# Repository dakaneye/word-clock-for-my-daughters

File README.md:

# word-clock-for-my-daughters

Two word clocks, one for each daughter, to be delivered around their 7th birthdays.

- **Emory** — Oct 6, 2030
- **Nora** — Mar 19, 2032

Shared ESP32 + WS2812B platform, per-kid configuration (name, birthday, wood species, lullaby, hidden birthdate acrostic).

See [`docs/superpowers/specs/2026-04-14-daughters-clocks-design.md`](docs/superpowers/specs/2026-04-14-daughters-clocks-design.md) for the full design.

## Lineage

Follows the original word clock for my wife Chelsea, built 2015 and revived 2026, at [`dakaneye/word-clock`](https://github.com/dakaneye/word-clock). Same family, newer generation.

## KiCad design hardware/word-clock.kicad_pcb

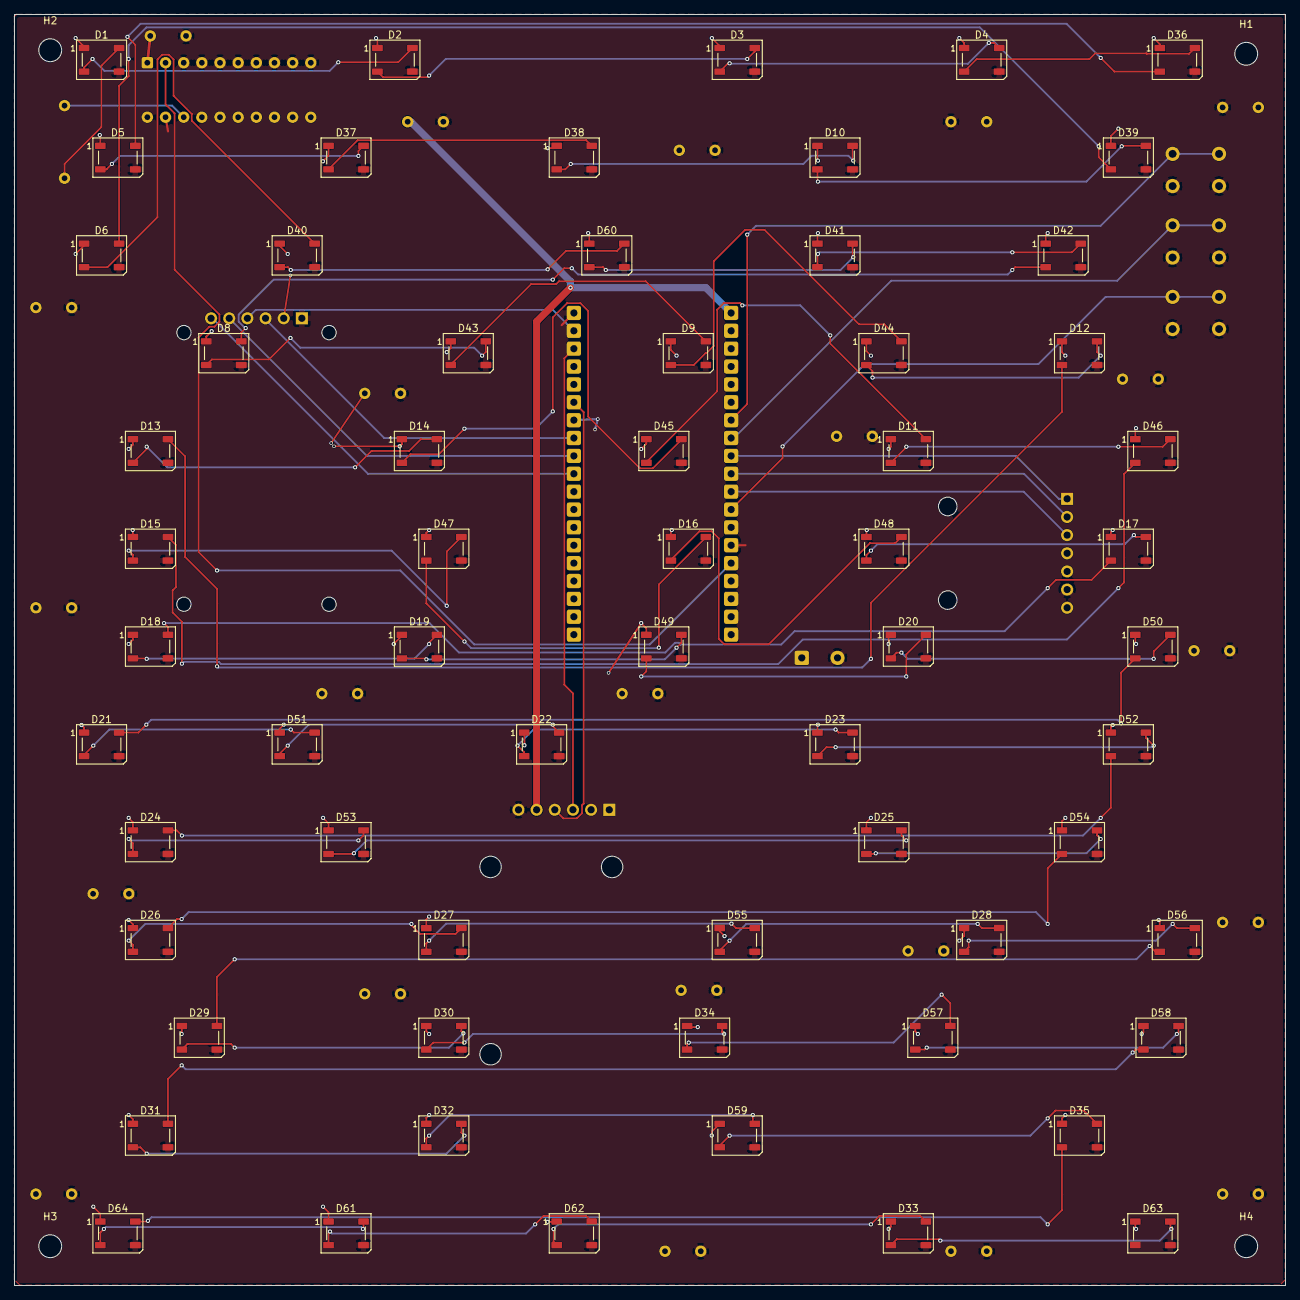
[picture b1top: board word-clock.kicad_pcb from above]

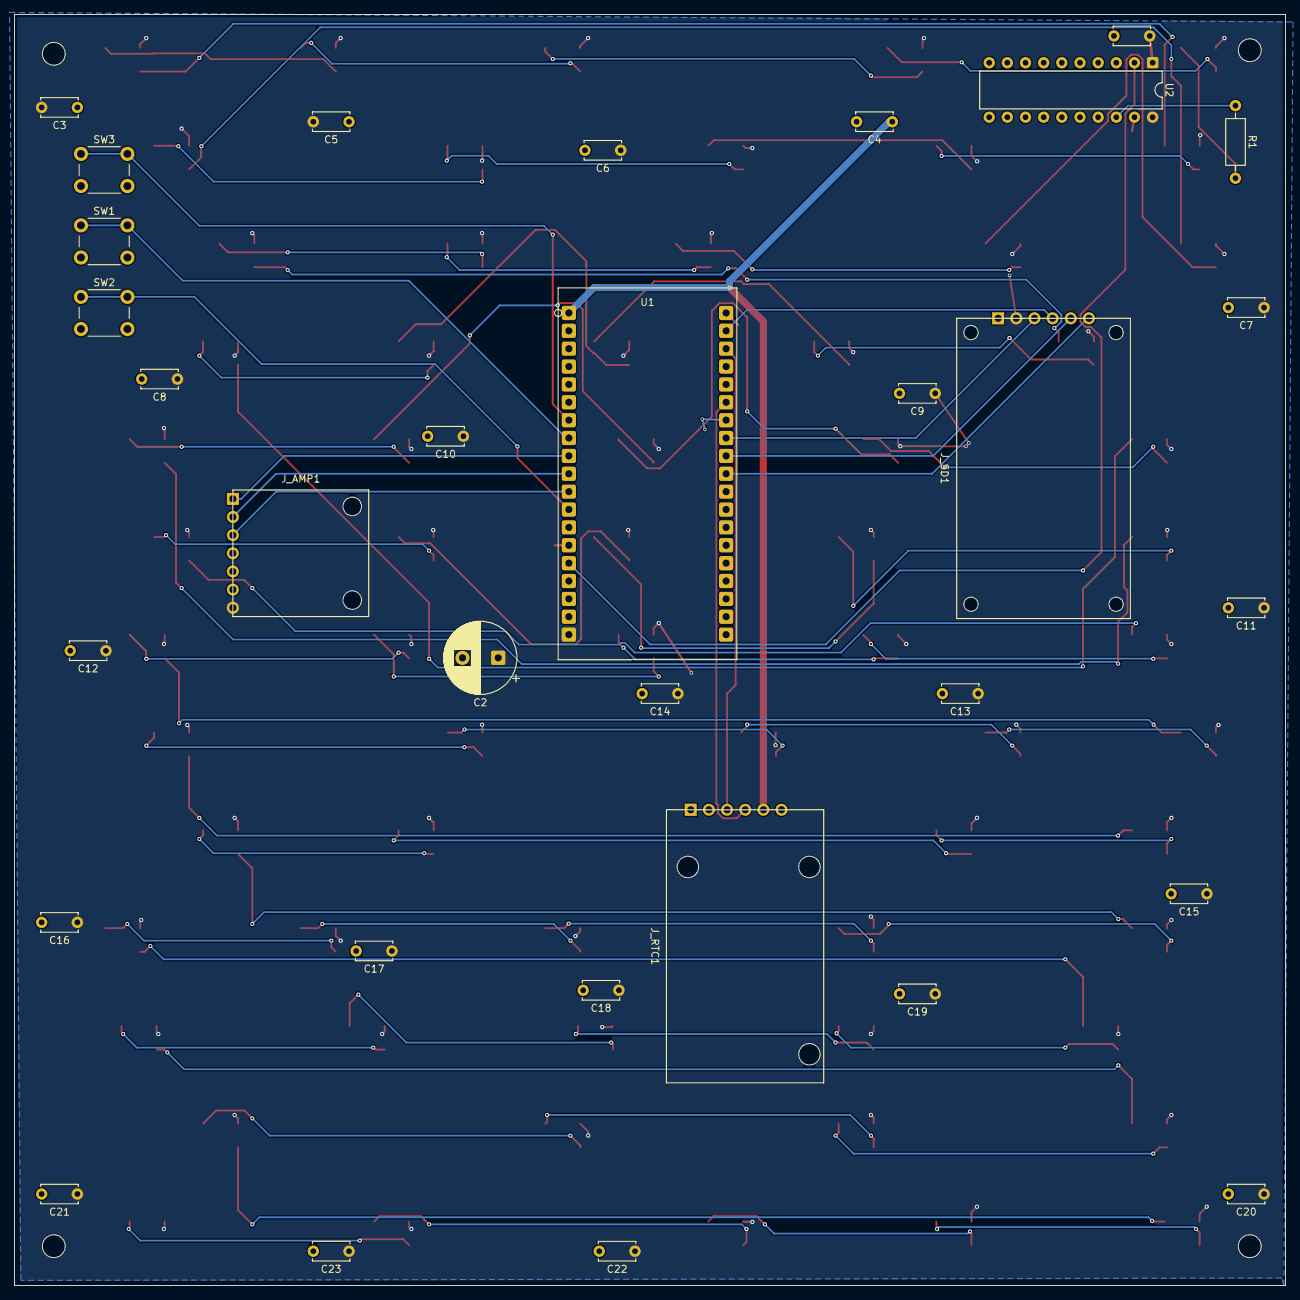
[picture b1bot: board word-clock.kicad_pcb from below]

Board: 2 copper layers, 177.8 x 177.8 mm, 99 parts (32 on the bottom side), 80 nets.

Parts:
C1, C3, C4, C5, C6, C7, C8, C9, C10, C11, C12, C13, C14, C15, C16, C17, C18, C19, C20, C21, C22, C23: 100nF; C_Disc_D5.0mm_W2.5mm_P5.00mm
C2: 1000µF / 10V; CP_Radial_D10.0mm_P5.00mm
D1: LED_IT; LED_WS2812B_PLCC4_5.0x5.0mm_P3.2mm
D2: LED_IS; LED_WS2812B_PLCC4_5.0x5.0mm_P3.2mm
D3: LED_TEN_MIN; LED_WS2812B_PLCC4_5.0x5.0mm_P3.2mm
D4: LED_HALF; LED_WS2812B_PLCC4_5.0x5.0mm_P3.2mm
D5: LED_QUARTER; LED_WS2812B_PLCC4_5.0x5.0mm_P3.2mm
D6: LED_FIVE_MIN; LED_WS2812B_PLCC4_5.0x5.0mm_P3.2mm
D8: LED_HAPPY; LED_WS2812B_PLCC4_5.0x5.0mm_P3.2mm
D9: LED_PAST; LED_WS2812B_PLCC4_5.0x5.0mm_P3.2mm
D10: LED_TWENTY; LED_WS2812B_PLCC4_5.0x5.0mm_P3.2mm
D11: LED_THREE; LED_WS2812B_PLCC4_5.0x5.0mm_P3.2mm
D12: LED_TO; LED_WS2812B_PLCC4_5.0x5.0mm_P3.2mm
D13: LED_ONE; LED_WS2812B_PLCC4_5.0x5.0mm_P3.2mm
D14: LED_BIRTH; LED_WS2812B_PLCC4_5.0x5.0mm_P3.2mm
D15: LED_ELEVEN; LED_WS2812B_PLCC4_5.0x5.0mm_P3.2mm
D16: LED_FOUR; LED_WS2812B_PLCC4_5.0x5.0mm_P3.2mm
D17: LED_DAY; LED_WS2812B_PLCC4_5.0x5.0mm_P3.2mm
D18: LED_TWO; LED_WS2812B_PLCC4_5.0x5.0mm_P3.2mm
D19: LED_EIGHT; LED_WS2812B_PLCC4_5.0x5.0mm_P3.2mm
D20: LED_SEVEN; LED_WS2812B_PLCC4_5.0x5.0mm_P3.2mm
D21: LED_NINE; LED_WS2812B_PLCC4_5.0x5.0mm_P3.2mm
D22: LED_SIX; LED_WS2812B_PLCC4_5.0x5.0mm_P3.2mm
D23: LED_TWELVE; LED_WS2812B_PLCC4_5.0x5.0mm_P3.2mm
D24: LED_NAME; LED_WS2812B_PLCC4_5.0x5.0mm_P3.2mm
D25: LED_FIVE_HR; LED_WS2812B_PLCC4_5.0x5.0mm_P3.2mm
D26: LED_TEN_HR; LED_WS2812B_PLCC4_5.0x5.0mm_P3.2mm
D27: LED_OCLOCK; LED_WS2812B_PLCC4_5.0x5.0mm_P3.2mm
D28: LED_NOON; LED_WS2812B_PLCC4_5.0x5.0mm_P3.2mm
D29: LED_IN; LED_WS2812B_PLCC4_5.0x5.0mm_P3.2mm
D30: LED_THE; LED_WS2812B_PLCC4_5.0x5.0mm_P3.2mm
D31: LED_AFTERNOON; LED_WS2812B_PLCC4_5.0x5.0mm_P3.2mm
D32: LED_AFTERNOON_1; LED_WS2812B_PLCC4_5.0x5.0mm_P3.2mm
D33: LED_NIGHT; LED_WS2812B_PLCC4_5.0x5.0mm_P3.2mm
D34: LED_MORNING; LED_WS2812B_PLCC4_5.0x5.0mm_P3.2mm
D35: LED_AT; LED_WS2812B_PLCC4_5.0x5.0mm_P3.2mm
D36: LED_HALF_1; LED_WS2812B_PLCC4_5.0x5.0mm_P3.2mm
D37: LED_QUARTER_1; LED_WS2812B_PLCC4_5.0x5.0mm_P3.2mm
D38: LED_QUARTER_2; LED_WS2812B_PLCC4_5.0x5.0mm_P3.2mm
D39: LED_TWENTY_1; LED_WS2812B_PLCC4_5.0x5.0mm_P3.2mm
D40: LED_FIVE_MIN_1; LED_WS2812B_PLCC4_5.0x5.0mm_P3.2mm
D41: LED_MINUTES_1; LED_WS2812B_PLCC4_5.0x5.0mm_P3.2mm
D42: LED_MINUTES_2; LED_WS2812B_PLCC4_5.0x5.0mm_P3.2mm
D43: LED_HAPPY_1; LED_WS2812B_PLCC4_5.0x5.0mm_P3.2mm
D44: LED_PAST_1; LED_WS2812B_PLCC4_5.0x5.0mm_P3.2mm
D45: LED_BIRTH_1; LED_WS2812B_PLCC4_5.0x5.0mm_P3.2mm
D46: LED_THREE_1; LED_WS2812B_PLCC4_5.0x5.0mm_P3.2mm
D47: LED_ELEVEN_1; LED_WS2812B_PLCC4_5.0x5.0mm_P3.2mm
D48: LED_FOUR_1; LED_WS2812B_PLCC4_5.0x5.0mm_P3.2mm
D49: LED_EIGHT_1; LED_WS2812B_PLCC4_5.0x5.0mm_P3.2mm
D50: LED_SEVEN_1; LED_WS2812B_PLCC4_5.0x5.0mm_P3.2mm
D51: LED_NINE_1; LED_WS2812B_PLCC4_5.0x5.0mm_P3.2mm
D52: LED_TWELVE_1; LED_WS2812B_PLCC4_5.0x5.0mm_P3.2mm
D53: LED_NAME_1; LED_WS2812B_PLCC4_5.0x5.0mm_P3.2mm
D54: LED_FIVE_HR_1; LED_WS2812B_PLCC4_5.0x5.0mm_P3.2mm
D55: LED_OCLOCK_1; LED_WS2812B_PLCC4_5.0x5.0mm_P3.2mm
D56: LED_NOON_1; LED_WS2812B_PLCC4_5.0x5.0mm_P3.2mm
D57: LED_MORNING_1; LED_WS2812B_PLCC4_5.0x5.0mm_P3.2mm
D58: LED_MORNING_2; LED_WS2812B_PLCC4_5.0x5.0mm_P3.2mm
D59: LED_AFTERNOON_2; LED_WS2812B_PLCC4_5.0x5.0mm_P3.2mm
D60: LED_MINUTES; LED_WS2812B_PLCC4_5.0x5.0mm_P3.2mm
D61: LED_EVENING_1; LED_WS2812B_PLCC4_5.0x5.0mm_P3.2mm
D62: LED_EVENING_2; LED_WS2812B_PLCC4_5.0x5.0mm_P3.2mm
D63: LED_NIGHT_1; LED_WS2812B_PLCC4_5.0x5.0mm_P3.2mm
D64: LED_EVENING; LED_WS2812B_PLCC4_5.0x5.0mm_P3.2mm
H1, H2, H3, H4: MountingHole_3.2mm_M3
J_AMP1: MAX98357A breakout; Daughtercard_AMP_MAX98357A
J_RTC1: DS3231 ZS-042; Daughtercard_RTC_DS3231
J_SD1: HW-125 microSD; Daughtercard_SD_HW125
R1: Resistor 300 ohm; R_Axial_DIN0207_L6.3mm_D2.5mm_P10.16mm_Horizontal
SW1: Minute; SW_PUSH_6mm
SW2: Audio; SW_PUSH_6mm
SW3: Hour; SW_PUSH_6mm
U1: ESP32 CP2102; ESP32_38Pin
U2: 74HCT245; DIP-20_W7.62mm

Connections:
+3V3: C4.1, J_RTC1.2 (VCC_5), U1.1 (3V3)
+5V: C1.1, C2.1, C3.2, C5.2, C6.1, C7.1, C8.1, C9.1, C10.1, C11.1, C12.1, C13.1, C14.1, C15.1, C16.1, C17.1, C18.1, C19.1, C20.1, C21.1, C22.1, C23.1, D1.1 (VDD), D2.1 (VDD), D3.1 (VDD), D4.1 (VDD), D5.1 (VDD), D6.1 (VDD), D8.1 (VDD), D9.1 (VDD), D10.1 (VDD), D11.1 (VDD), D12.1 (VDD), D13.1 (VDD), D14.1 (VDD), D15.1 (VDD), D16.1 (VDD), D17.1 (VDD), D18.1 (VDD), D19.1 (VDD), D20.1 (VDD), D21.1 (VDD), D22.1 (VDD), D23.1 (VDD), D24.1 (VDD), D25.1 (VDD), D26.1 (VDD), D27.1 (VDD), D28.1 (VDD), D29.1 (VDD), D30.1 (VDD), D31.1 (VDD), D32.1 (VDD), D33.1 (VDD), D34.1 (VDD), D35.1 (VDD), D36.1 (VDD), D37.1 (VDD), D38.1 (VDD), D39.1 (VDD), D40.1 (VDD), D41.1 (VDD), D42.1 (VDD), D43.1 (VDD), D44.1 (VDD), D45.1 (VDD), D46.1 (VDD), D47.1 (VDD), D48.1 (VDD), D49.1 (VDD), D50.1 (VDD), D51.1 (VDD), D52.1 (VDD), D53.1 (VDD), D54.1 (VDD), D55.1 (VDD), D56.1 (VDD), D57.1 (VDD), D58.1 (VDD), D59.1 (VDD), D60.1 (VDD), D61.1 (VDD), D62.1 (VDD), D63.1 (VDD), D64.1 (VDD), J_AMP1.7 (VIN), J_SD1.5 (VCC_2), U1.19 (V5), U2.1 (A->B), U2.20 (VCC)
/BTN_AUDIO: SW2.1, U1.12 (GPIO14)
/BTN_HOUR: SW3.1, U1.7 (GPIO32)
/BTN_MINUTE: SW1.1, U1.8 (GPIO33)
/I2C_SCL: J_RTC1.4 (SCL_3), U1.36 (GPIO22)
/I2C_SDA: J_RTC1.3 (SDA_4), U1.33 (GPIO21)
/I2S_BCLK: J_AMP1.2 (BCLK), U1.10 (GPIO26)
/I2S_DIN: J_AMP1.3 (DIN), U1.11 (GPIO27)
/I2S_LRC: J_AMP1.1 (LRC), U1.9 (GPIO25)
/LED_DATA_3V3: U1.15 (GPIO13), U2.2 (A0)
/LED_DATA_5V: R1.1, U2.18 (B0)
/LED_DATA_OUT: D1.4 (DIN), R1.2
/SD_CS: J_SD1.1 (CS_6), U1.29 (GPIO5)
/SD_MISO: J_SD1.4 (MISO_3), U1.31 (GPIO19)
/SD_MOSI: J_SD1.3 (MOSI_4), U1.37 (GPIO23)
/SD_SCK: J_SD1.2 (SCK_5), U1.30 (GPIO18)
GND: C1.2, C2.2, C3.1, C4.2, C5.1, C6.2, C7.2, C8.2, C9.2, C10.2, C11.2, C12.2, C13.2, C14.2, C15.2, C16.2, C17.2, C18.2, C19.2, C20.2, C21.2, C22.2, C23.2, D1.3 (VSS), D2.3 (VSS), D3.3 (VSS), D4.3 (VSS), D5.3 (VSS), D6.3 (VSS), D8.3 (VSS), D9.3 (VSS), D10.3 (VSS), D11.3 (VSS), D12.3 (VSS), D13.3 (VSS), D14.3 (VSS), D15.3 (VSS), D16.3 (VSS), D17.3 (VSS), D18.3 (VSS), D19.3 (VSS), D20.3 (VSS), D21.3 (VSS), D22.3 (VSS), D23.3 (VSS), D24.3 (VSS), D25.3 (VSS), D26.3 (VSS), D27.3 (VSS), D28.3 (VSS), D29.3 (VSS), D30.3 (VSS), D31.3 (VSS), D32.3 (VSS), D33.3 (VSS), D34.3 (VSS), D35.3 (VSS), D36.3 (VSS), D37.3 (VSS), D38.3 (VSS), D39.3 (VSS), D40.3 (VSS), D41.3 (VSS), D42.3 (VSS), D43.3 (VSS), D44.3 (VSS), D45.3 (VSS), D46.3 (VSS), D47.3 (VSS), D48.3 (VSS), D49.3 (VSS), D50.3 (VSS), D51.3 (VSS), D52.3 (VSS), D53.3 (VSS), D54.3 (VSS), D55.3 (VSS), D56.3 (VSS), D57.3 (VSS), D58.3 (VSS), D59.3 (VSS), D60.3 (VSS), D61.3 (VSS), D62.3 (VSS), D63.3 (VSS), D64.3 (VSS), J_AMP1.6 (GND), J_RTC1.1 (GND_6), J_SD1.6 (GND_1), SW1.2, SW2.2, SW3.2, U1.14 (GND), U1.32 (GND), U1.38 (GND), U2.3 (A1), U2.4 (A2), U2.5 (A3), U2.6 (A4), U2.7 (A5), U2.8 (A6), U2.9 (A7), U2.10 (GND), U2.19 (CE)
unnamed: D1.2 (DOUT), D2.4 (DIN)
unnamed: D2.2 (DOUT), D3.4 (DIN)
unnamed: D3.2 (DOUT), D4.4 (DIN)
unnamed: D10.4 (DIN), D38.2 (DOUT)
unnamed: D10.2 (DOUT), D39.4 (DIN)
unnamed: D11.4 (DIN), D45.2 (DOUT)
unnamed: D11.2 (DOUT), D46.4 (DIN)
unnamed: D12.4 (DIN), D44.2 (DOUT)
unnamed: D12.2 (DOUT), D13.4 (DIN)
unnamed: D13.2 (DOUT), D14.4 (DIN)
unnamed: D14.2 (DOUT), D45.4 (DIN)
unnamed: D15.4 (DIN), D46.2 (DOUT)
unnamed: D15.2 (DOUT), D47.4 (DIN)
unnamed: D16.4 (DIN), D47.2 (DOUT)
unnamed: D16.2 (DOUT), D48.4 (DIN)
unnamed: D17.4 (DIN), D48.2 (DOUT)
unnamed: D17.2 (DOUT), D18.4 (DIN)
unnamed: D18.2 (DOUT), D19.4 (DIN)
unnamed: D19.2 (DOUT), D49.4 (DIN)
unnamed: D20.4 (DIN), D49.2 (DOUT)
unnamed: D20.2 (DOUT), D50.4 (DIN)
unnamed: D21.4 (DIN), D50.2 (DOUT)
unnamed: D21.2 (DOUT), D51.4 (DIN)
unnamed: D22.4 (DIN), D51.2 (DOUT)
unnamed: D22.2 (DOUT), D23.4 (DIN)
unnamed: D23.2 (DOUT), D52.4 (DIN)
unnamed: D24.4 (DIN), D52.2 (DOUT)
unnamed: D24.2 (DOUT), D53.4 (DIN)
unnamed: D25.4 (DIN), D53.2 (DOUT)
unnamed: D25.2 (DOUT), D54.4 (DIN)
unnamed: D26.4 (DIN), D54.2 (DOUT)
unnamed: D26.2 (DOUT), D27.4 (DIN)
unnamed: D27.2 (DOUT), D55.4 (DIN)
unnamed: D28.4 (DIN), D55.2 (DOUT)
unnamed: D28.2 (DOUT), D56.4 (DIN)
unnamed: D29.4 (DIN), D56.2 (DOUT)
unnamed: D29.2 (DOUT), D30.4 (DIN)
unnamed: D30.2 (DOUT), D34.4 (DIN)
unnamed: D31.4 (DIN), D58.2 (DOUT)
unnamed: D31.2 (DOUT), D32.4 (DIN)
unnamed: D32.2 (DOUT), D59.4 (DIN)
unnamed: D33.4 (DIN), D62.2 (DOUT)
unnamed: D33.2 (DOUT), D63.4 (DIN)
unnamed: D34.2 (DOUT), D57.4 (DIN)
unnamed: D35.4 (DIN), D59.2 (DOUT)
unnamed: D35.2 (DOUT), D64.4 (DIN)
unnamed: D4.2 (DOUT), D36.4 (DIN)
unnamed: D5.4 (DIN), D36.2 (DOUT)
unnamed: D5.2 (DOUT), D37.4 (DIN)
unnamed: D37.2 (DOUT), D38.4 (DIN)
unnamed: D6.4 (DIN), D39.2 (DOUT)
unnamed: D6.2 (DOUT), D40.4 (DIN)
unnamed: D40.2 (DOUT), D60.4 (DIN)
unnamed: D41.4 (DIN), D60.2 (DOUT)
unnamed: D41.2 (DOUT), D42.4 (DIN)
unnamed: D8.4 (DIN), D42.2 (DOUT)
unnamed: D8.2 (DOUT), D43.4 (DIN)
unnamed: D9.4 (DIN), D43.2 (DOUT)
unnamed: D9.2 (DOUT), D44.4 (DIN)
unnamed: D57.2 (DOUT), D58.4 (DIN)
unnamed: D61.4 (DIN), D64.2 (DOUT)
unnamed: D61.2 (DOUT), D62.4 (DIN)

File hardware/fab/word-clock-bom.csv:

Comment,Designator,Footprint,LCSC Part #
WS2812B-B/W,"D1,D2,D3,D4,D5,D6,D8,D9,D10,D11,D12,D13,D14,D15,D16,D17,D18,D19,D20,D21,D22,D23,D24,D25,D26,D27,D28,D29,D30,D31,D32,D33,D34,D35,D36,D37,D38,D39,D40,D41,D42,D43,D44,D45,D46,D47,D48,D49,D50,D51,D52,D53,D54,D55,D56,D57,D58,D59,D60,D61,D62,D63,D64",LED_WS2812B_PLCC4_5.0x5.0mm_P3.2mm,C114586

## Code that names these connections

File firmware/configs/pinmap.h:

// firmware/configs/pinmap.h
//
// Shared GPIO pin assignments for every Phase 2 firmware module.
// Source of truth: docs/hardware/pinout.md §Firmware constants.
//
// The `configs/` directory is on the ESP32 envs' -I include path via
// `[esp32-base] build_flags = -I configs` in platformio.ini, so any
// Arduino-env source can `#include "pinmap.h"`. Native/pure-logic code
// never includes this header — it doesn't touch hardware.
#pragma once

// WS2812B LED strip
#define PIN_LED_DATA     13

// DS3231 RTC (I²C default pins)
#define PIN_I2C_SDA      21
#define PIN_I2C_SCL      22

// microSD card (VSPI)
#define PIN_SD_CS         5
#define PIN_SD_MOSI      23
#define PIN_SD_MISO      19
#define PIN_SD_CLK       18

// MAX98357A I²S amplifier
#define PIN_I2S_BCLK     26
#define PIN_I2S_LRC      25
#define PIN_I2S_DIN      27

// Tact switches (INPUT_PULLUP, other leg to GND)
#define PIN_BUTTON_HOUR   32
#define PIN_BUTTON_MINUTE 33
#define PIN_BUTTON_AUDIO  14

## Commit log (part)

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2026-04-15 docs: initial design spec for Emory and Nora word clocks
    Scaffolds the new repo for the daughters' clocks. Spec drafted in the original word-clock repo during the brainstorming session; moved here to own the new project's history cleanly.
2026-04-15 fix(firmware): unset board for native env to avoid esp32dev resolution
2026-04-15 ci: bump actions/cache from 4 to 5
    Bumps [actions/cache](https://github.com/actions/cache) from 4 to 5.
    - [Release notes](https://github.com/actions/cache/releases)
    - [Changelog](https://github.com/actions/cache/blob/main/RELEASES.md)
    - [Commits](https://github.com/actions/cache/compare/v4...v5)
    ---
    updated-dependencies:
2026-04-15 ci: drop job name fields so check contexts match sync tool expectations
2026-04-15 feat(firmware): holiday palette lookup with easter and nth-weekday
2026-04-15 docs: correct sd card pricing note (32gb same price as 4gb)
2026-04-15 docs: research on esp32 boot, usb-c cc resistors, fastled+esp32
2026-04-15 docs: revert level shifter guide to 74HCT245 (matches placed symbol)
2026-04-15 docs: renumber pcb guide phases and drop time estimates
2026-04-15 feat(hardware): footprints assigned; esp32 swif7ify library added
2026-04-16 docs: single rework guide for led reorder + AT fix + finish pcb
2026-04-16 docs: laser-cut face spec + implementation plan
2026-04-16 feat(enclosure): Ponoko SVG conventions module
2026-04-16 feat(enclosure): frame strip outline path with two finger edges
2026-04-16 refactor(enclosure): deduplicate frame + drop cardboard test
    Emory and Nora frames are byte-identical (render_frame_svg takes no
    kid parameter — geometry is the same). Merged to one frame.svg;
    the kid-specific distinction is the wood material selected when
    uploading to Ponoko, not the SVG content.
    Cardboard test variant removed — the test didn't de-risk the actual
    failure modes (hardwood grain, kerf, scorching) because cardboard
2026-04-16 fix(enclosure): multiple strut bugs — interior positions, arrow effect, sliver holes
    Found via self-review using cairosvg local rendering:
    1. A's H strut at x_frac=0.3 was INTERIOR (entirely inside counter) — had
    zero effect on the cut. The letter was only getting connected via the
    V strut which caused the 'arrow' effect. Moved H to x_frac=0 boundary.
    2. A's V strut at bottom of counter was non-structural: upper counter
    island can't connect to outside-A wood through the below-crossbar area
2026-04-16 fix(enclosure): preserve beziers on non-strut letters + buffer(0) for B
    Two issues were causing bezier-splash artifacts in the rendered faces:
    1. Every glyph went through flatten → shapely union → reserialize, which
    turned Fraunces's serif curves into zigzag polylines. Added a fast path
    that returns the raw path untouched when the letter has no strut rule
    and is a single subpath — covers ~half the Fraunces alphabet.
    2. Self-intersecting paths (Jost B packs outer + 2 counters into one
2026-04-16 docs(hardware): bottom-side component heights + standoff budget
    Table of every bottom-side footprint with estimated heights from package
    datasheets + common daughterboard / header standards. Tallest feature is
    the MAX98357A screw-terminal variant at ~19 mm. Recommended back-panel
    standoff: 20 mm, leaving ~18 mm of depth for the light-channel honeycomb
    inside the 48 mm frame — comfortably above the ≥14 mm LED-spacing minimum
    for uniform diffusion.
2026-04-16 fix(enclosure): back-panel USB cutout sized for a panel-mount adapter
    The USB-C-female-to-Micro-USB-male rigid adapter user picked has its own
    aluminum body with integrated M2 screw tabs flanking a narrow USB-C
    receptacle face. It mounts directly to the inside of the back panel,
    replacing both the previously-planned panel-mount pigtail AND the
    separate internal-adapter cradle. Its Micro-USB male end connects to the
    ESP32 via a short commodity Micro-USB male-to-female extension cable.
2026-04-16 docs: snapshot state — all Ponoko SVGs ordered, parts en route tomorrow
    Rewrites TODO.md to reflect the current state:
    - All three fabricated-wood parts (faces, frames, back panels) ordered
    from Ponoko. Only supplies + PCB + 3D prints + assembly remain.
    - Architecture section now captures every locked decision from this
    session (bare frame, captive USB cable, corner hex-spacer attachment,
    daughterboard orientation).
2026-04-17 style(firmware): wrap build_src_filter for readability
2026-04-17 feat(firmware): captive portal form HTML + CSS
2026-04-17 feat(firmware): wifi_provision main module + lifecycle
2026-04-17 feat(enclosure): build123d setup + pcb standoff post
2026-04-17 feat(firmware): add shared pinmap.h for phase 2 modules
2026-04-17 feat(firmware): public buttons module API + event enum
2026-04-17 docs(firmware): manual hardware checks for buttons module
2026-04-17 refactor(firmware): json escape + dead-code cleanup
    Post-review-2 polish:
    - web_server: consolidate JSON string escaping into json_escape() and route
    both /status and /scan SSIDs through it. /status response was previously
    unescaped (safe today, but would break if confirmation_message ever
    includes user-controlled text). /scan SSID was partially escaped inline;
    json_escape also handles control chars and newlines.
2026-04-17 docs(todo): petg diffuser decision + flag remaining phase 2 spec gaps
2026-04-17 feat(firmware): display led_map — WordId to PCB chain index
2026-04-17 build(clangd): blanket-suppress diagnostics in test/ path
    The diagnostic-by-ID list was never going to converge. Native-env
    test files live outside compile_commands.json (which covers only
    emory), so clangd's fallback compiler mixes ESP32 toolchain headers
    with macOS libc++ and trips on stdlib internals that have nothing
    to do with the code. `pio test -e native` is the authoritative
    signal; silence clangd in test/ to stop the noise.
2026-04-17 feat(firmware): scaffold display renderer (warm white path)
2026-04-17 feat(firmware): display ESP32 adapter + FastLED power cap
2026-04-17 feat(firmware): rtc scaffold + DateTime struct
2026-04-17 docs(todo): mark rtc module complete
2026-04-18 feat(firmware): pure-logic is_plausible_epoch (ntp)
2026-04-18 feat(firmware): bring-up wire-up of ntp in main.cpp
2026-04-19 feat(firmware): audio module scaffold (empty stubs)
2026-04-19 docs: flip audio file format MP3 → WAV + add audio spec ref
2026-04-19 fix(firmware): clock face free-runs on RTC during WiFi drops
    Parent spec §Time sync promises "No WiFi: free-runs on DS3231.
    Drift is low (seconds per week) — acceptable." The previous main.cpp
    gated ALL display rendering on wifi_provision::state() == Online,
    which meant a router reboot or captive-portal re-entry blanked the
    clock face entirely for 30-300 s of reconnect backoff. Visibly
    violates the spec.
2026-04-20 test: add Tier 1 structural pytest for /scan polling (red)
2026-04-20 feat(captive-portal): poll /scan every 2s with 30s timeout + refresh
    Replaces the one-shot fetch('/scan') with a polling state machine. Stops
    on first non-empty response (critical: server WiFi.scanDelete()s after
    serving results, so a second poll would return [] and erase the
    dropdown). After 30s of empty/failed responses, shows 'No networks found
    — click Refresh' plus a Refresh button that restarts polling.
    Tier 1 pytest (6) + Tier 2 Playwright (5) now green.
2026-04-20 feat(wifi_provision): keep AP up during Validating + 5s online grace
    Before this change, pressing Audio tore down the AP immediately on
    entry to Validating — killing the web server. The "Connected!" status
    the /status endpoint was designed to return during Online state was
    unreachable; the user's captive-portal page went blank with no success
    feedback, producing the "did the button work?" confusion on bench
    bring-up 2026-04-20.
2026-04-21 docs: hardware doc sweep from 2026-04-20 bench bring-up
    Rolling up doc edits made across the bring-up session:
    - pinout.md: caliper-verified heights for MAX98357A, DS3231, HW-125,
    and ESP32 module (all under estimates by 0.7-5.7mm); softened the
    "always remove charging resistor" FUD now that the 3.3V reverse-
    bias physics + replacement-cadence mitigation is captured.
    - assembly-plan.md: long-term maintenance section with the CR2032
2026-04-21 perf(main): throttle display render to ~30 Hz
    At full loop speed (~1 kHz given the trailing delay(1)) the display was
    re-rendering 1000 times per second — pure waste. Also saturated the
    ESP32 enough that UART serial output became garbled during bench-tests
    (the settimeofday fix commit lit the display, which immediately made
    the render loop run constantly).
    30 Hz is plenty for the only animated element (birthday rainbow, 60 s
2026-04-21 docs(todo): record button-cap design + no-cradle speaker plan
    Button cap design shipped as enclosure/3d/button_cap.py, ready to
    slice once printer arrives. Speaker mount pivoted from a
    3D-printed cradle to 2 M3 × 10 mm brass hex spacers (from the
    existing 10-pack for the corner mounts) glued to the back panel
    interior — brass-on-epoxy outlasts PLA-on-epoxy for the 40-year
    horizon, and the speaker stays removable. Added a line item for
2026-05-02 fix(audio): reconcile spec + tests with implementation
    - Spec note about Playing/Birth + BirthdayFired said "None-action no-op"
    but the table row and implementation both return SwitchFile (benign
    re-open). Update the note to match; the table was correct.
    - Extend test_playing_lullaby_birthday_switches_to_birth to also cover
    Track::Birth (was previously only LullabyOne/LullabyTwo).
    - Spec failure-handling table: i2s_write non-OK error now correctly
2026-05-06 fix(display): correct led_map for actual PCB chain routing
    The auto-router did not lay the chain in D-numerical order — it minimized
    trace length, so D5 → D10 → D6 → D7 → D8 → D9 → D12 → D13 → D14 → D11 →
    D15. Earlier "D-number minus 1" map matched the breadboard wiring but
    not the production PCB, lighting wrong words at runtime (e.g. firmware
    PAST lit physical D8 = HAPPY). Map now derived by walking the chain in
    hardware/word-clock.kicad_pcb directly.
2026-06-13 feat(hardware): commit as-fabricated 63-LED board
    The 63-LED board ordered from JLCPCB 2026-06-07 lived only in the working
    tree and an untracked fab zip; the last hardware commit was the
    superseded 35-LED April design. Commit the canonical KiCad source, the
    custom daughtercard footprints (word-clock.pretty/ + fp-lib-table), and
    the exact as-ordered fab package so the design that became the physical
    clocks is under version control for the 40-year horizon.
2026-06-13 chore(hardware): track regenerated 63-LED master BOM
    The master BOM (hardware/word-clock.csv) that CLAUDE.md names the source
    of truth was gitignored and stale (35-LED topology, empty part columns).
    Replace it with a current as-built BOM regenerated from the 63-LED KiCad
    source: 63 WS2812B-V6 LEDs (D7 unused), 22x 100nF + 1x 1000uF, R1, the
    three daughtercard modules, 3 buttons, ESP32, and U2 74HCT245. LCSC is
    filled for the JLC-placed LED (C52917433); hand-soldered parts are noted
2026-06-15 fix(rtc,display): guard RTC reads + fix amber false-trigger
    Cluster 5 review findings:
    - rtc::now() returned RTClib's uninitialized read buffer as valid time on
    an I2C NAK / bus glitch. Guard with DateTime::isValid() and fall back to
    the last good reading so the face freezes for a tick instead of painting
    garbage.
    - The amber stale-sync tint tripped on a perfectly healthy clock: the
2026-06-16 fix(wifi_provision): persist per-AP submit rate limit
    reset_submit_state(reset_rate_limit=false) was dead: fail_validation()
    calls start_ap() -> web::begin() first, and begin() unconditionally zeroed
    submit_count, so wrong-password submit -> confirm -> fail cycles never
    accumulated toward MAX_SUBMITS and the documented 429 lockout was
    unreachable. Stop resetting submit_count in begin(); it is 0 at boot
    (static init) and after reset_to_captive()'s restart, and is cleared only
